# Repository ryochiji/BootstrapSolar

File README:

Open Source design files for BootstrapSolar projects.

See http://bootstrapsolar.com

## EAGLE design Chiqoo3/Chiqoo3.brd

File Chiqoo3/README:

Chiqoo v3 (working name)

Status: Development (not tested)

This version assumes input of 3.5 - 4.2V, and use with LiFePO4 batteries only. Uses a fuse for over-current protection, and zener diodes for over-voltage protection.

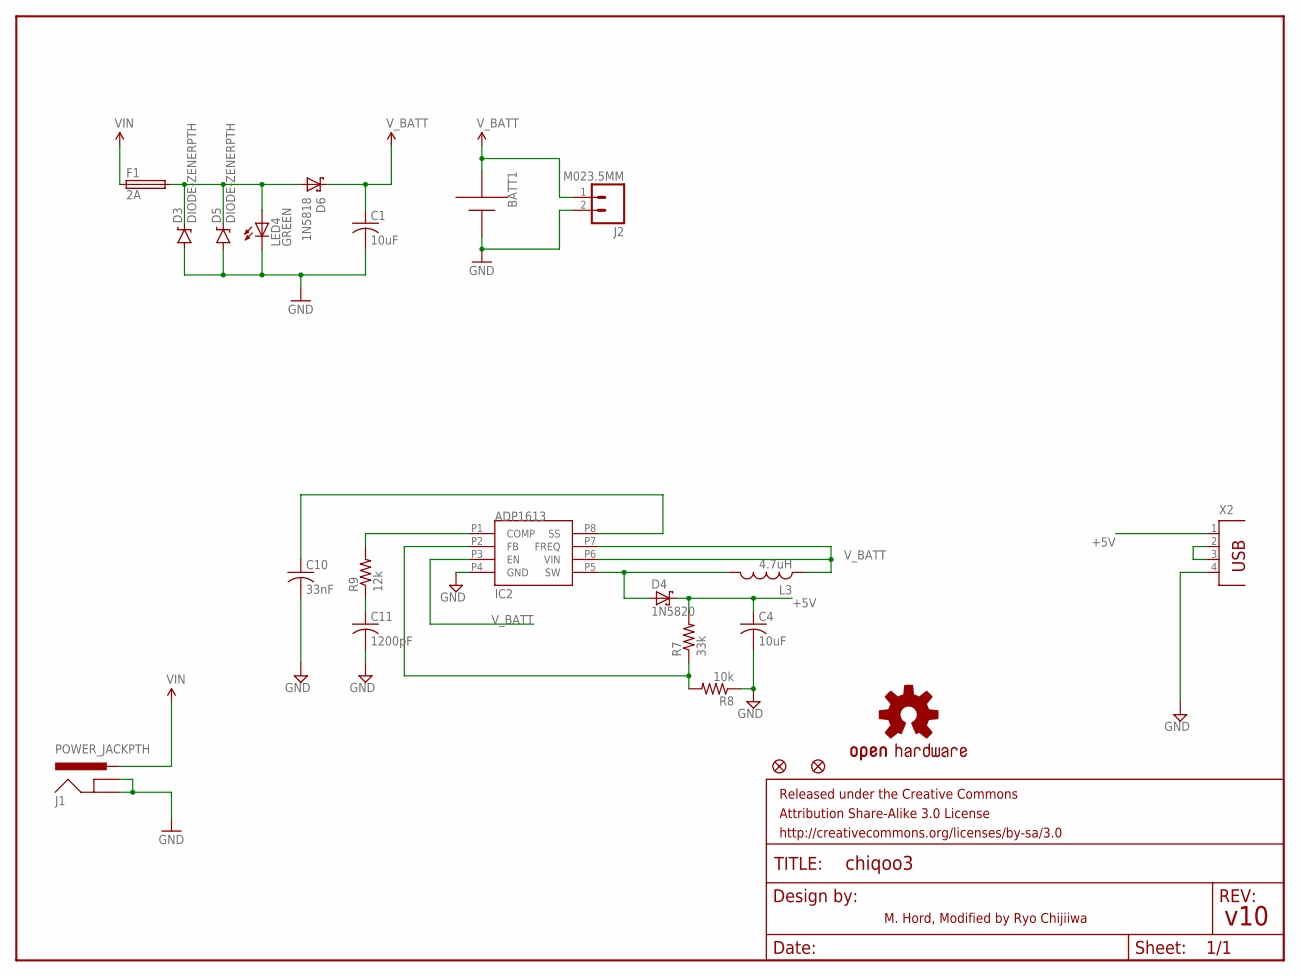
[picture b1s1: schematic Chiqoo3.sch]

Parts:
BATT1: 18650-HOLDER; BK-18650-PC2
C1, C4: 10uF; C050-024X044
C10: 33nF; C050-024X044
C11: 1200pF; C025-025X050
D3, D5: DIODE-ZENERPTH; DIODE-ZENER
D4: 1N5820; DIODE
D6: 1N5818; DIODE-5
F1: 2A; TE5
FID1, FID2: FIDUCIAL1X2; FIDUCIAL-1X2
FRAME1: FRAME-LETTER; CREATIVE_COMMONS
IC2: ADP1613; RM-8
J1: POWER_JACKPTH; POWER_JACK_PTH
J2: M023.5MM; SCREWTERMINAL-3.5MM-2
L3: 4.7uH; L-5MM-THRUHOLE
LED4: GREEN; LED3MM
LOGO2: OSHW-LOGOM; OSHW-LOGO-M
R7: 33k; 0204/5
R8: 10k; 0204/5
R9: 12k; 0204/5
X2: PN87520

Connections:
5V1: D4.ANNODE (A), IC2.P5 (SW), L3.2
+5V: C4.1, D4.CATHODE (C), R7.2, X2.1
GND: BATT1.- (--), C1.2, C4.2, C10.2, C11.2, D3.P$2 (A), D5.P$2 (A), IC2.P4 (GND), J1.GND, J1.GNDBREAK, J2.2, LED4.K (C), R8.1, X2.4
unnamed: IC2.P1 (COMP), R9.2
unnamed: X2.2, X2.3
unnamed: C11.1, R9.1
unnamed: IC2.P2 (FB), R7.1, R8.2
unnamed: C10.1, IC2.P8 (SS)
unnamed: D3.P$1 (C), D5.P$1 (C), D6.A, F1.2, LED4.A
VIN: F1.1, J1.PWR
V_BATT: BATT1.+ (++), C1.1, D6.C, IC2.P3 (EN), IC2.P6 (VIN), IC2.P7 (FREQ), J2.1, L3.1

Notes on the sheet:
v10
M. Hord, Modified by Ryo Chijiiwa

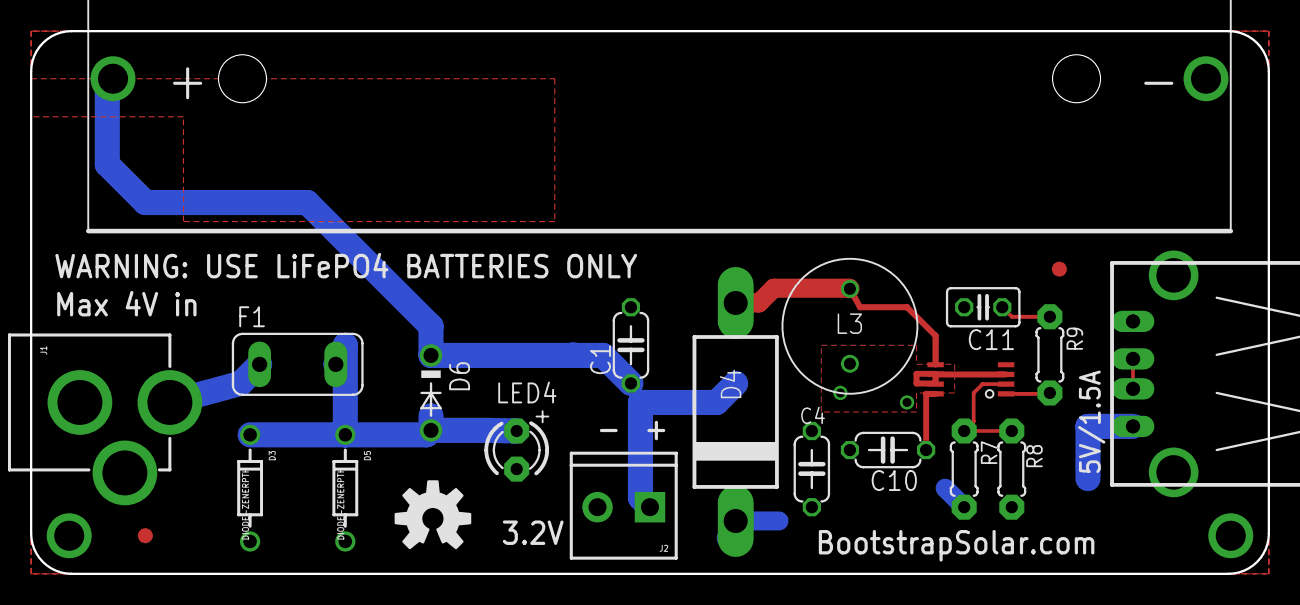
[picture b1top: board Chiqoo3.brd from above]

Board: 2 copper layers, 82.5 x 36.2 mm, 23 parts (0 on the bottom side), 11 nets.

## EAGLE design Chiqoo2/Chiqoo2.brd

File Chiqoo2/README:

Chiqoo v2 (working name)

Solar charger/light. Supports 6~20V input, 5V output at up to 1.5A via USB. Two-onboard LEDs for lighting.

BOM at: https://docs.google.com/spreadsheets/d/16bUJoE1ZQbacxXeRS_gSl4m6bO_L1ZmG7trxUfU6TPQ/edit?usp=sharing

Based on pre-existing Open Source designs:
SunnyBuddy - https://www.sparkfun.com/products/12084
BootstrapSolar USB power boost - https://github.com/ryochiji/BootstrapSolar/tree/master/USBPowerBoost

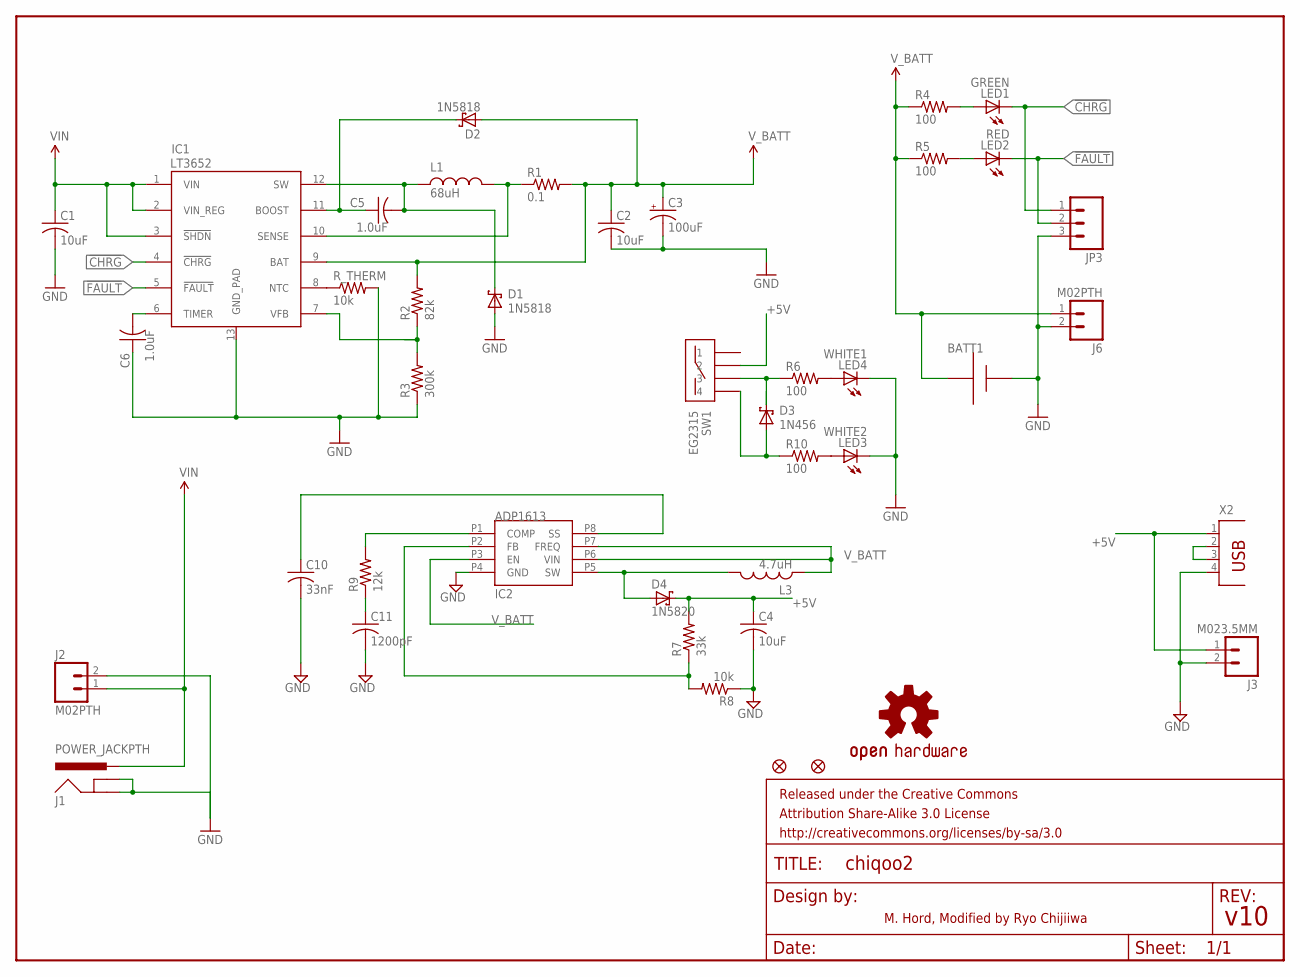
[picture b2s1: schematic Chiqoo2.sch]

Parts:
BATT1: 18650-HOLDER; BK-18650-PC2
C1, C2, C4: 10uF; C050-024X044
C3: 100uF; E5-5
C5, C6: 1.0uF; C025-025X050
C10: 33nF; C050-024X044
C11: 1200pF; C025-025X050
D1, D2: 1N5818; DIODE-5
D3: 1N456; DIODE-5
D4: 1N5820; DIODE
FID1, FID2: FIDUCIAL1X2; FIDUCIAL-1X2
FRAME1: FRAME-LETTER; CREATIVE_COMMONS
IC1: LT3652; MSOP-12_GND
IC2: ADP1613; RM-8
J1: POWER_JACKPTH; POWER_JACK_PTH
J2, J6: M02PTH; 1X02
J3: M023.5MM; SCREWTERMINAL-3.5MM-2
JP3: M03PTH; 1X03
L1: 68uH; L-5MM-THRUHOLE
L3: 4.7uH; L-5MM-THRUHOLE
LED1: GREEN; LED3MM
LED2: RED; LED3MM
LED3: WHITE2; LED5MM
LED4: WHITE1; LED5MM
LOGO2: OSHW-LOGOM; OSHW-LOGO-M
R1: 0.1; 0204/5
R2: 82k; 0204/5
R3: 300k; 0204/5
R4, R5, R6, R10: 100; 0204/5
R7: 33k; 0204/5
R8: 10k; 0204/5
R9: 12k; 0204/5
R_THERM: 10k; 0204/5
SW1: EG2315
X2: PN87520

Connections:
5V1: D4.ANNODE (A), IC2.P5 (SW), L3.2
!CHRG: IC1.4 (!CHRG), JP3.1, LED1.K (C)
!FAULT: IC1.5 (!FAULT), JP3.2, LED2.K (C)
+5V: C4.1, D4.CATHODE (C), J3.1, R7.2, SW1.2, SW1.6 (2), X2.1
BOOST: C5.1, D2.C, IC1.11 (BOOST)
FB: IC1.7 (VFB), R2.1, R3.2
GND: BATT1.- (--), C1.2, C2.2, C3.-, C4.2, C6.1, C10.2, C11.2, D1.A, IC1.13 (GND_PAD), IC2.P4 (GND), J1.GND, J1.GNDBREAK, J2.2, J3.2, J6.2, JP3.3, LED3.K (C), LED4.K (C), R3.1, R8.1, R_THERM.2, X2.4
unnamed: IC1.8 (NTC), R_THERM.1
unnamed: LED1.A, R4.2
unnamed: IC2.P1 (COMP), R9.2
unnamed: LED2.A, R5.2
unnamed: X2.2, X2.3
unnamed: C11.1, R9.1
unnamed: IC2.P2 (FB), R7.1, R8.2
unnamed: C10.1, IC2.P8 (SS)
unnamed: D3.C, R6.1, SW1.3, SW1.7 (3)
unnamed: LED4.A, R6.2
unnamed: LED3.A, R10.2
unnamed: D3.A, R10.1, SW1.4, SW1.8 (4)
SENSE: IC1.10 (SENSE), L1.2, R1.1
SW: C5.2, D1.C, IC1.12 (SW), L1.1
TIMER: C6.2, IC1.6 (TIMER)
VIN: C1.1, IC1.1 (VIN), IC1.2 (VIN_REG), IC1.3 (!SHDN), J1.PWR, J2.1
V_BATT: BATT1.+ (++), C2.1, C3.+, D2.A, IC1.9 (BAT), IC2.P3 (EN), IC2.P6 (VIN), IC2.P7 (FREQ), J6.1, L3.1, R1.2, R2.2, R4.1, R5.1

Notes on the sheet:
v10
M. Hord, Modified by Ryo Chijiiwa

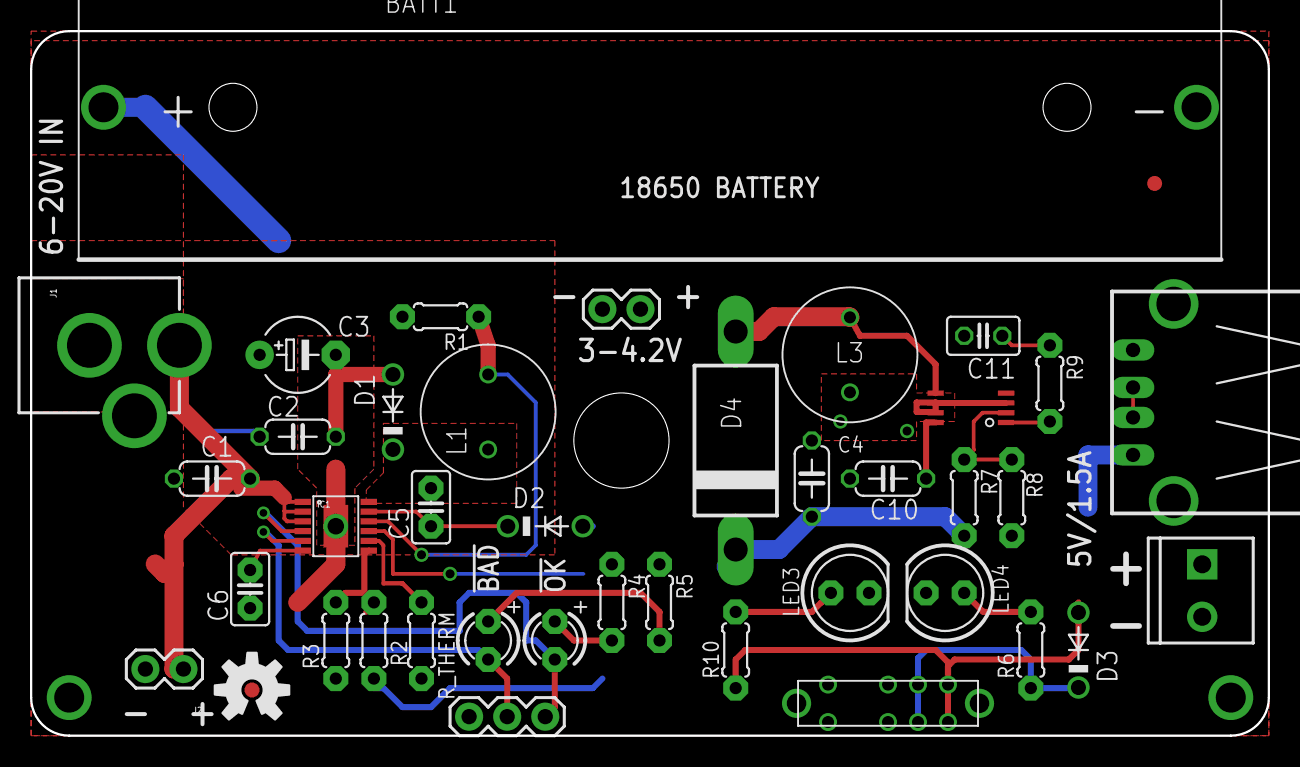
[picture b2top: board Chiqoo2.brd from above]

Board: 2 copper layers, 82.5 x 47.0 mm, 43 parts (0 on the bottom side), 24 nets.

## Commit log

2011-10-04 added EagleLibs/README
2011-10-04 added SolarLipoCharger designs
2011-10-04 added USBPowerBoost designs
2011-10-04 added eagle libs
2011-10-04 README changes
2011-10-04 added todo
2011-10-16 added USBPowerBoost_SMD_v0_1_5
2011-10-17 added license to README
2011-10-20 updated USBPowerBoost_SMD
2011-11-26 Final prod version
2011-11-26 Prod version
2014-07-10 initial commit of Chiqoo2 Eagle files
2014-07-15 initial commit of README
2014-07-15 fixed status light labels
2014-07-15 bunch o updates with components for the Chiqoo2
2014-09-18 Chiqoo2 fixes
2014-09-18 initial commit of Chiqoo3
2014-09-18 added Chiqoo3 README

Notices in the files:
parts and their libraries:
SparkFun-Aesthetics: Licensing: CC v3.0 Share-Alike You are welcome to use this library for commercial purposes.
SparkFun-Aesthetics: Released under the Creative Commons Attribution Share-Alike 3.0 License
SparkFun-Aesthetics: http://creativecommons.org/licenses/by-sa/3.0
